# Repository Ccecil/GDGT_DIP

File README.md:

This is a breakout board for the Smoothieboard V2 which allows a Gadgeteer connection which has a 4 input DIP switch and 3 debounced switch inputs with ESD protection. 

Schematic here: [GDGT_DIP.pdf](https://github.com/user-attachments/files/24159001/GDGT_DIP.pdf)

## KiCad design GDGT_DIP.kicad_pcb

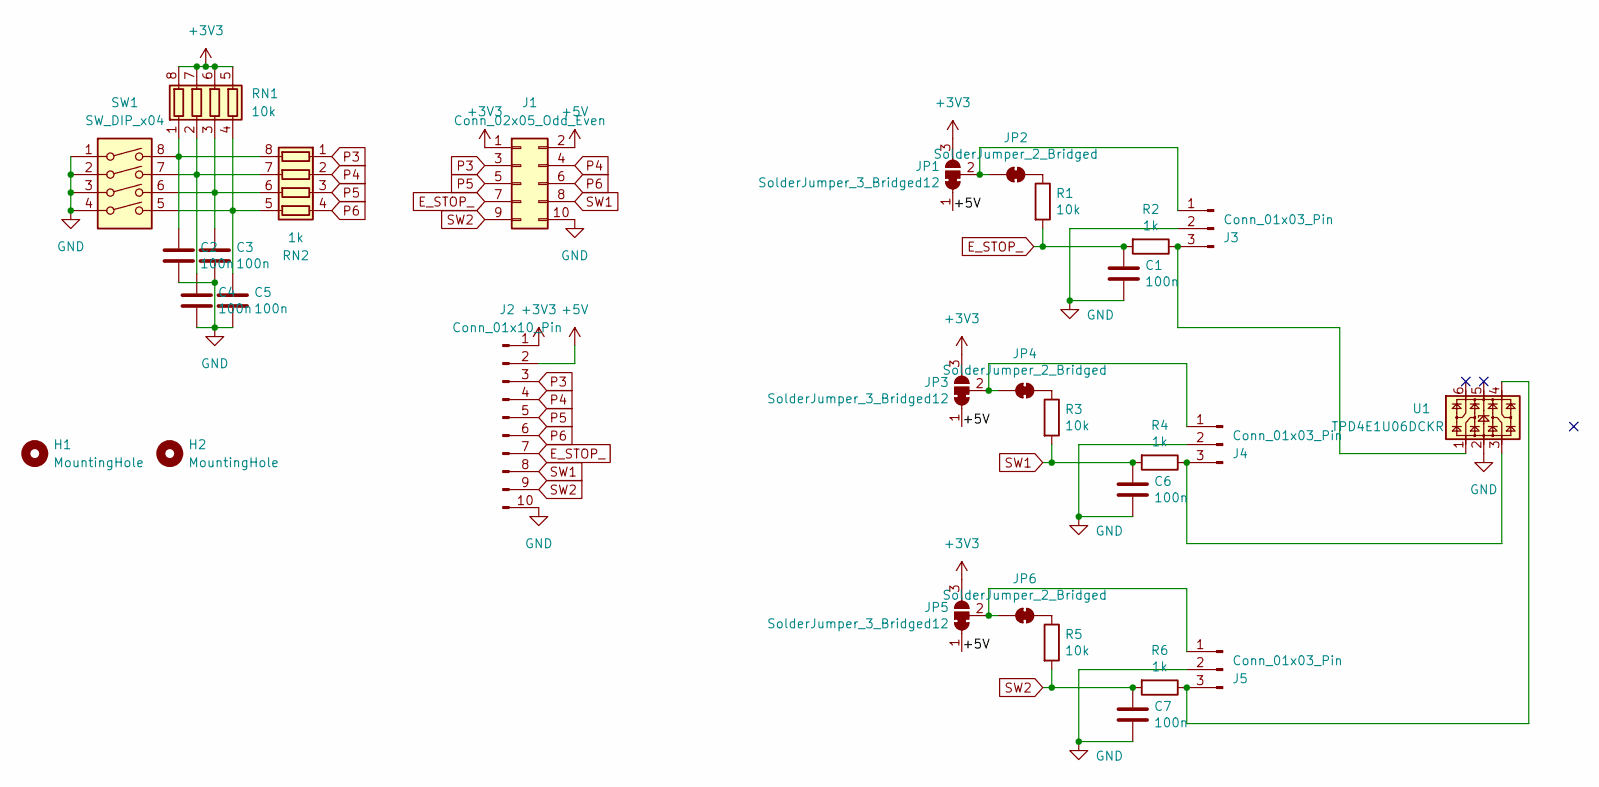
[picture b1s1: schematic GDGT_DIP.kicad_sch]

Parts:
C1, C2, C3, C4, C5, C6, C7: 100n; C_0402_1005Metric
H1, H2: MountingHole; MountingHole_3.2mm_M3
J1: Conn_02x05_Odd_Even; PinHeader_2x05_P1.27mm_Vertical_SMD
J2: Conn_01x10_Pin; PinHeader_1x10_P2.54mm_Vertical
J3, J4, J5: Conn_01x03_Pin; Molex_KK-254_AE-6410-03A_1x03_P2.54mm_Vertical
JP1, JP3, JP5: SolderJumper_3_Bridged12; SolderJumper-3_P1.3mm_Bridged12_RoundedPad1.0x1.5mm
JP2, JP4, JP6: SolderJumper_2_Bridged; SolderJumper-2_P1.3mm_Bridged2Bar_RoundedPad1.0x1.5mm
R1, R3, R5: 10k; R_0402_1005Metric
R2, R4, R6: 1k; R_0402_1005Metric
RN1: 10k; R_Array_Concave_4x0603
RN2: 1k; R_Array_Concave_4x0603
SW1: SW_DIP_x04; SW_DIP_SPSTx04_Slide_9.78x12.34mm_W7.62mm_P2.54mm
U1: TPD4E1U06DCKR; SOT-363_SC-70-6

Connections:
+3V3: J1.1, J2.1, JP1.3 (B), JP3.3 (B), JP5.3 (B), RN1.5 (R4.2), RN1.6 (R3.2), RN1.7 (R2.2), RN1.8 (R1.2)
+5V: J1.2, J2.2, JP1.1 (A), JP3.1 (A), JP5.1 (A)
E_STOP_: C1.1, J1.7, J2.7, R1.2, R2.2
GND: C1.2, C2.2, C3.2, C4.2, C5.2, C6.2, C7.2, J1.10, J2.10, J3.2, J4.2, J5.2, SW1.1, SW1.2, SW1.3, SW1.4, U1.2
unnamed: J3.1, JP1.2 (C), JP2.1 (A)
unnamed: J3.3, R2.1, U1.1
unnamed: J4.1, JP3.2 (C), JP4.1 (A)
unnamed: J4.3, R4.1, U1.3
unnamed: J5.1, JP5.2 (C), JP6.1 (A)
unnamed: J5.3, R6.1, U1.4
unnamed: JP2.2 (B), R1.1
unnamed: JP4.2 (B), R3.1
unnamed: JP6.2 (B), R5.1
unnamed: C2.1, RN1.1 (R1.1), RN2.8 (R1.2), SW1.8
unnamed: C4.1, RN1.2 (R2.1), RN2.7 (R2.2), SW1.7
unnamed: C3.1, RN1.3 (R3.1), RN2.6 (R3.2), SW1.6
unnamed: C5.1, RN1.4 (R4.1), RN2.5 (R4.2), SW1.5
P3: J1.3, J2.3, RN2.1 (R1.1)
P4: J1.4, J2.4, RN2.2 (R2.1)
P5: J1.5, J2.5, RN2.3 (R3.1)
P6: J1.6, J2.6, RN2.4 (R4.1)
SW1: C6.1, J1.8, J2.8, R3.2, R4.2
SW2: C7.1, J1.9, J2.9, R5.2, R6.2

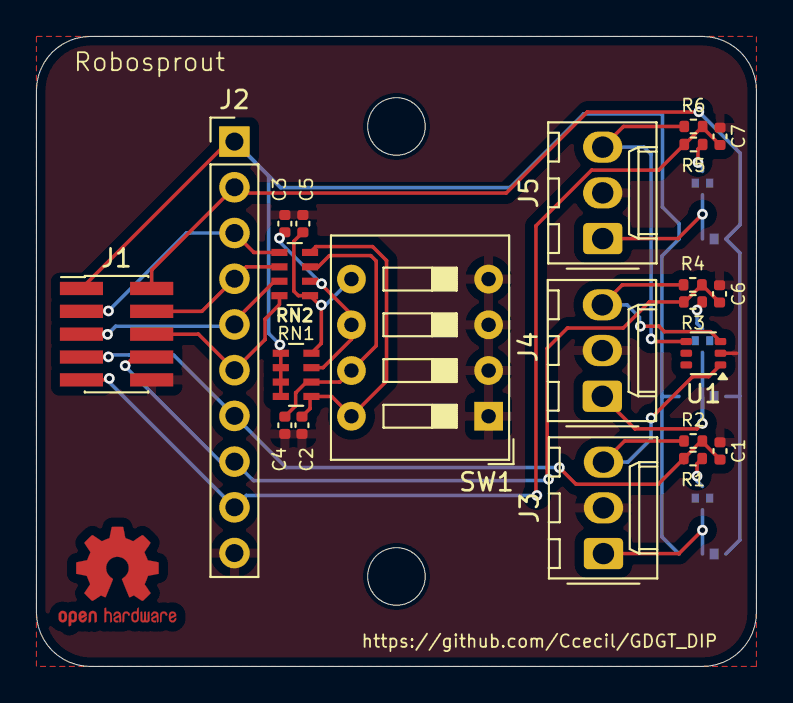
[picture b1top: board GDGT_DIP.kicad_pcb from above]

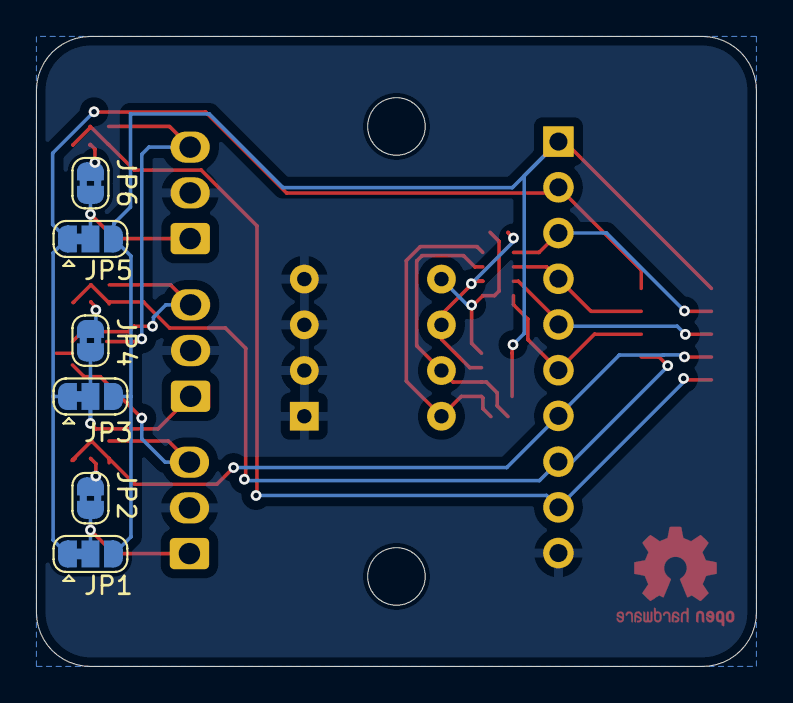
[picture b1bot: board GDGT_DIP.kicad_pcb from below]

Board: 2 copper layers, 40.0 x 35.0 mm, 30 parts (6 on the bottom side), 23 nets.

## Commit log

2025-12-15 Initial upload
